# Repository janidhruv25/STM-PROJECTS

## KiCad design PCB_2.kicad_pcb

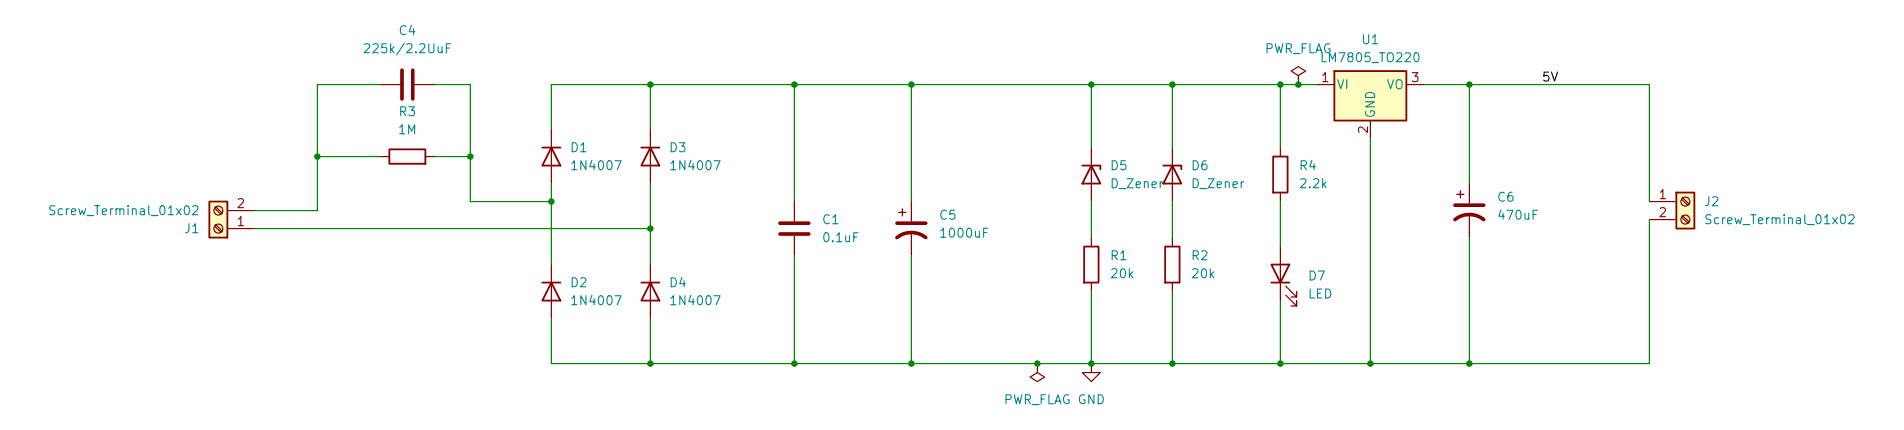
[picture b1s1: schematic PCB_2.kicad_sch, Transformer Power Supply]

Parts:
C1: 0.1uF; C_Disc_D4.7mm_W2.5mm_P5.00mm
C4: 225k/2.2UuF; C_Rect_L18.0mm_W6.0mm_P15.00mm_FKS3_FKP3
C5: 1000uF; CP_Radial_D10.0mm_P5.00mm
C6: 470uF; CP_Radial_D10.0mm_P3.80mm
D1, D2, D3, D4: 1N4007; D_DO-41_SOD81_P10.16mm_Horizontal
D5, D6: D_Zener; D_A-405_P7.62mm_Horizontal
D7: LED; LED_D5.0mm
J1, J2: Screw_Terminal_01x02; TerminalBlock_MaiXu_MX126-5.0-02P_1x02_P5.00mm
R1, R2: 20k; D_A-405_P7.62mm_Horizontal
R3: 1M; D_A-405_P7.62mm_Horizontal
R4: 2.2k; D_A-405_P7.62mm_Horizontal
U1: LM7805_TO220; TO-220-3_Vertical

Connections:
/5V: C6.1, J2.1, U1.3 (VO)
GND: C1.2, C5.2, C6.2, D2.2 (A), D4.2 (A), D7.1 (K), J2.2, R1.2, R2.2, U1.2 (GND)
unnamed: C4.2, D1.2 (A), D2.1 (K), R3.2
unnamed: C1.1, C5.1, D1.1 (K), D3.1 (K), D5.1 (K), D6.1 (K), R4.1, U1.1 (VI)
unnamed: D3.2 (A), D4.1 (K), J1.1
unnamed: D5.2 (A), R1.1
unnamed: D6.2 (A), R2.1
unnamed: D7.2 (A), R4.2
unnamed: C4.1, J1.2, R3.1

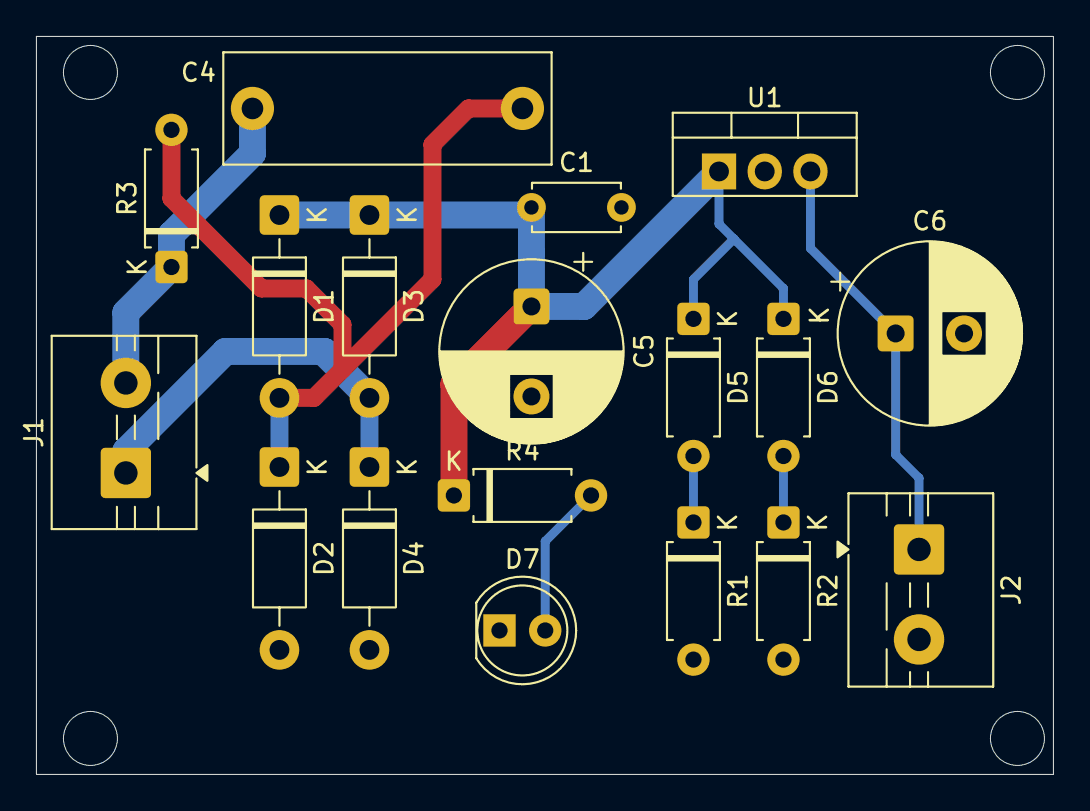
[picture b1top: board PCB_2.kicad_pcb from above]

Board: 2 copper layers, 56.5 x 41.0 mm, 18 parts (0 on the bottom side), 9 nets.
